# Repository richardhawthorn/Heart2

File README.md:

### Description

LED Heart

<div id="link">
	<a href="http://www.deluxecapacitor.com/projects/view/16">Project Page</a>
</div>

### Features

- 16 LED display
- Charlieplex LED control
- ATTINY44 processor
- 3V operation @ 1Mhz or 8Mhz
- 1x button
- ICSP port
- Holes for necklace chain

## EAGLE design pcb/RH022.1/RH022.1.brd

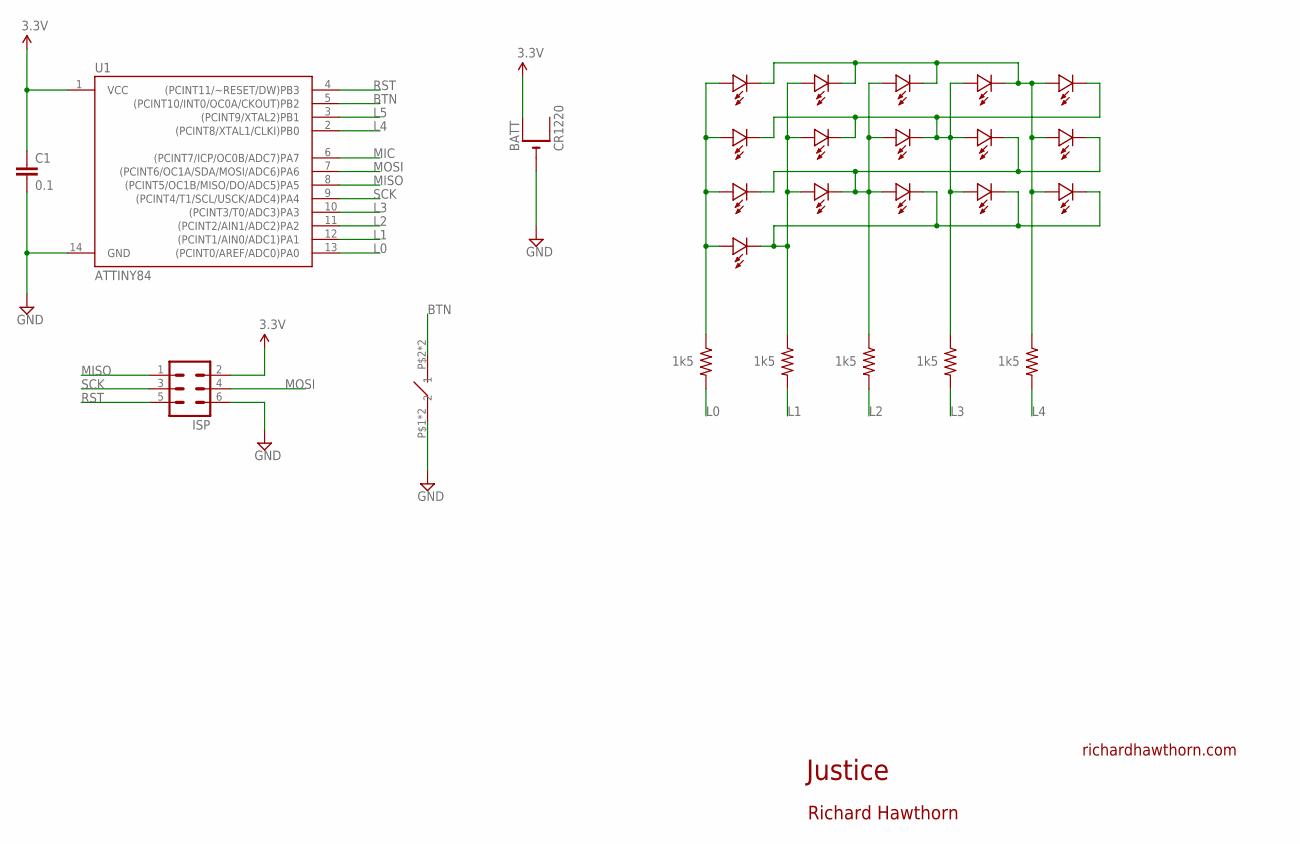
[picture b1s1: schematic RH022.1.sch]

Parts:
BATT: CR1220; CR1220-SMD
BTN1: TURTLE-3PIN
C1: 0.1; 0603-CAP
ISP: MA03-2
LED1, LED2, LED3, LED4, LED5, LED6, LED7, LED8, LED9, LED10, LED11, LED12, LED13, LED14, LED15, LED16: LED0603; 0603-LED
R1, R2, R3, R4, R5: 1k5; 0603-RES
U1: ATTINY84; SO14

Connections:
BTN: BTN1.P$2 (2), BTN1.P$4 (2), U1.5 ((PCINT10/INT0/OC0A/CKOUT)PB2)
GND: BATT.-, BTN1.P$1 (1), BTN1.P$3 (1), C1.2, ISP.6, U1.14 (GND)
L0: R1.2, U1.13 ((PCINT0/AREF/ADC0)PA0)
L1: R2.2, U1.12 ((PCINT1/AIN0/ADC1)PA1)
L2: R3.2, U1.11 ((PCINT2/AIN1/ADC2)PA2)
L3: R4.2, U1.10 ((PCINT3/T0/ADC3)PA3)
L4: R5.2, U1.2 ((PCINT8/XTAL1/CLKI)PB0)
L5: U1.3 ((PCINT9/XTAL2)PB1)
MIC: U1.6 ((PCINT7/ICP/OC0B/ADC7)PA7)
MISO: ISP.1, U1.8 ((PCINT5/OC1B/MISO/DO/ADC5)PA5)
MOSI: ISP.4, U1.7 ((PCINT6/OC1A/SDA/MOSI/ADC6)PA6)
unnamed: LED2.PLUS, LED7.PLUS, LED12.PLUS, LED13.MINUS, LED14.MINUS, LED15.MINUS, LED16.MINUS, R2.1
unnamed: LED1.PLUS, LED6.PLUS, LED11.PLUS, LED16.PLUS, R1.1
unnamed: LED1.MINUS, LED2.MINUS, LED3.MINUS, LED4.MINUS, LED5.PLUS, LED10.PLUS, LED15.PLUS, R5.1
unnamed: LED4.PLUS, LED5.MINUS, LED6.MINUS, LED7.MINUS, LED8.MINUS, LED9.PLUS, LED14.PLUS, R4.1
unnamed: LED3.PLUS, LED8.PLUS, LED9.MINUS, LED10.MINUS, LED11.MINUS, LED12.MINUS, LED13.PLUS, R3.1
RST: ISP.5, U1.4 ((PCINT11/~RESET/DW)PB3)
SCK: ISP.3, U1.9 ((PCINT4/T1/SCL/USCK/ADC4)PA4)
VCC: BATT.+$1 (+), C1.1, ISP.2, U1.1 (VCC)

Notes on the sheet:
Justice
richardhawthorn.com
Richard Hawthorn

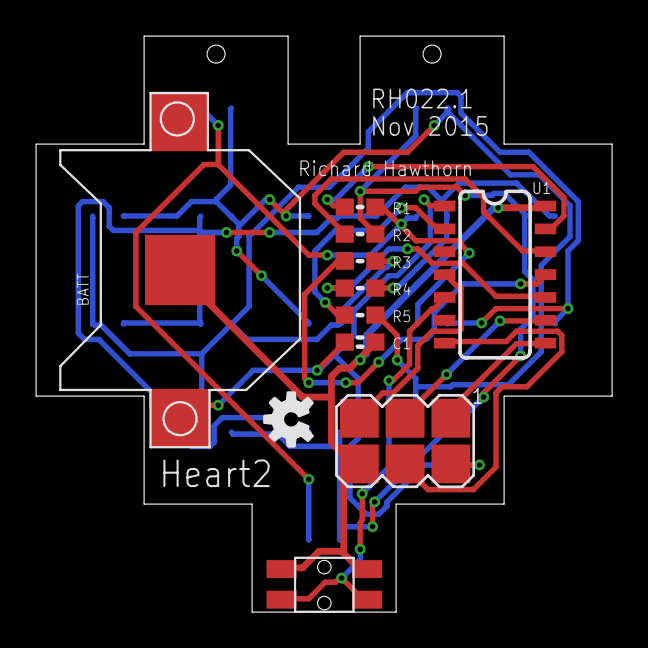
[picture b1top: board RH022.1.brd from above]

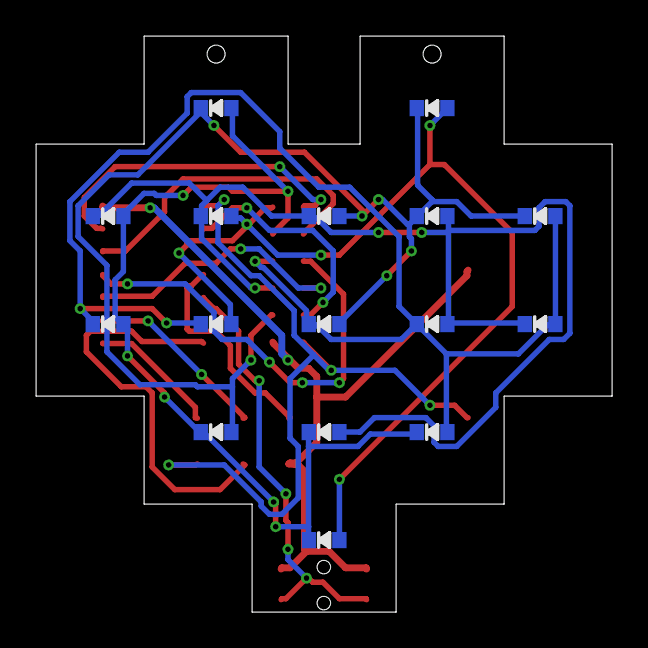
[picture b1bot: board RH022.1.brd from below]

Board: 2 copper layers, 32.0 x 32.0 mm, 27 parts (16 on the bottom side), 17 nets.

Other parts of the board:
U$3: OSHW-LOGO-S

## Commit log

2015-11-10 first version of the pcb
2015-11-10 added gerbers
2015-11-10 added images
2016-01-01 Adding Photos
2016-01-02 update image
2016-01-02 add readme
2016-01-02 add the arduino code
2016-01-03 update gitignore

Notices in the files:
parts and their libraries:
SparkFun-Aesthetics: Licensing: CC v3.0 Share-Alike You are welcome to use this library for commercial purposes.
SparkFun-DigitalIC: Licensing: Creative Commons ShareAlike 4.0 International - https://creativecommons.org/licenses/by-sa/4.0
